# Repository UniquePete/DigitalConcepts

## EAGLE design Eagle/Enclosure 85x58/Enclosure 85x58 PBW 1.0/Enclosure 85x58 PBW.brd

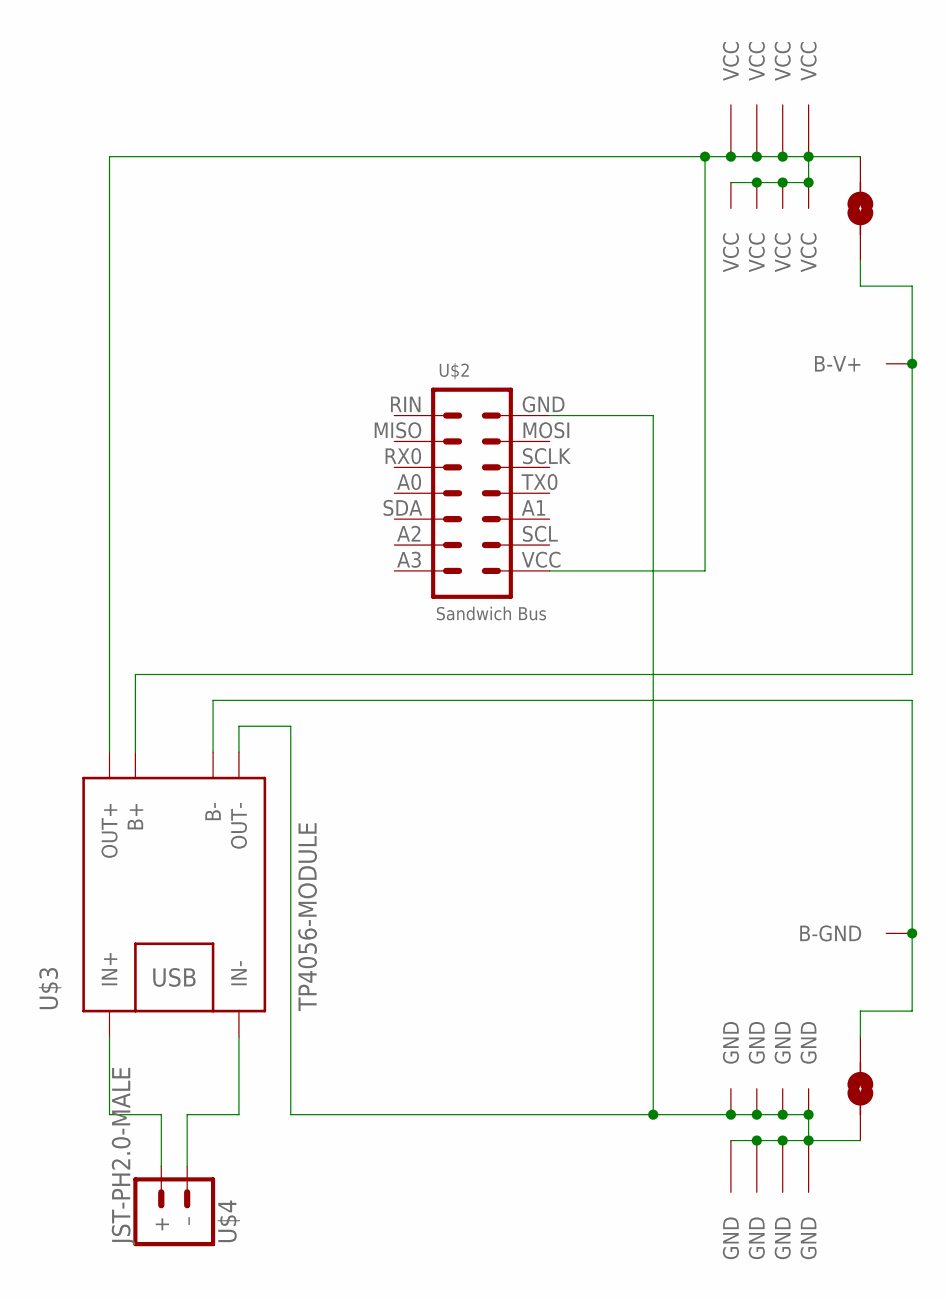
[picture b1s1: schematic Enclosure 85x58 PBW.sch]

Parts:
U$1: PROTO-28X18-BAT2-SJ-W
U$2: Sandwich Bus; CONN_2X7-WIJNAND-PROCESSOR
U$3: TP4056-MODULE; BATTERY-CHARGER-LI-PROT
U$4: JST-PH2.0-MALE; JST-PH2.0

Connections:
GND: U$1.GND@SJ (GND), U$1.P27-11 (GND), U$1.P27-12 (GND), U$1.P27-13 (GND), U$1.P27-14 (GND), U$1.P28-11 (GND), U$1.P28-12 (GND), U$1.P28-13 (GND), U$1.P28-14 (GND), U$2.GND (7), U$3.OUT-
unnamed: U$1.B-GND@SJ (B-GND), U$1.P25-16 (B-GND), U$3.B-
unnamed: U$1.B-V+@SJ (B-V+), U$1.P03-16 (B-V+), U$3.B+
unnamed: U$3.IN+, U$4.+
unnamed: U$3.IN-, U$4.- (–)
VCC: U$1.P01-11 (VCC), U$1.P01-12 (VCC), U$1.P01-13 (VCC), U$1.P01-14 (VCC), U$1.P02-11 (VCC), U$1.P02-12 (VCC), U$1.P02-13 (VCC), U$1.P02-14 (VCC), U$1.VCC@SJ (VCC), U$2.VCC (1), U$3.OUT+

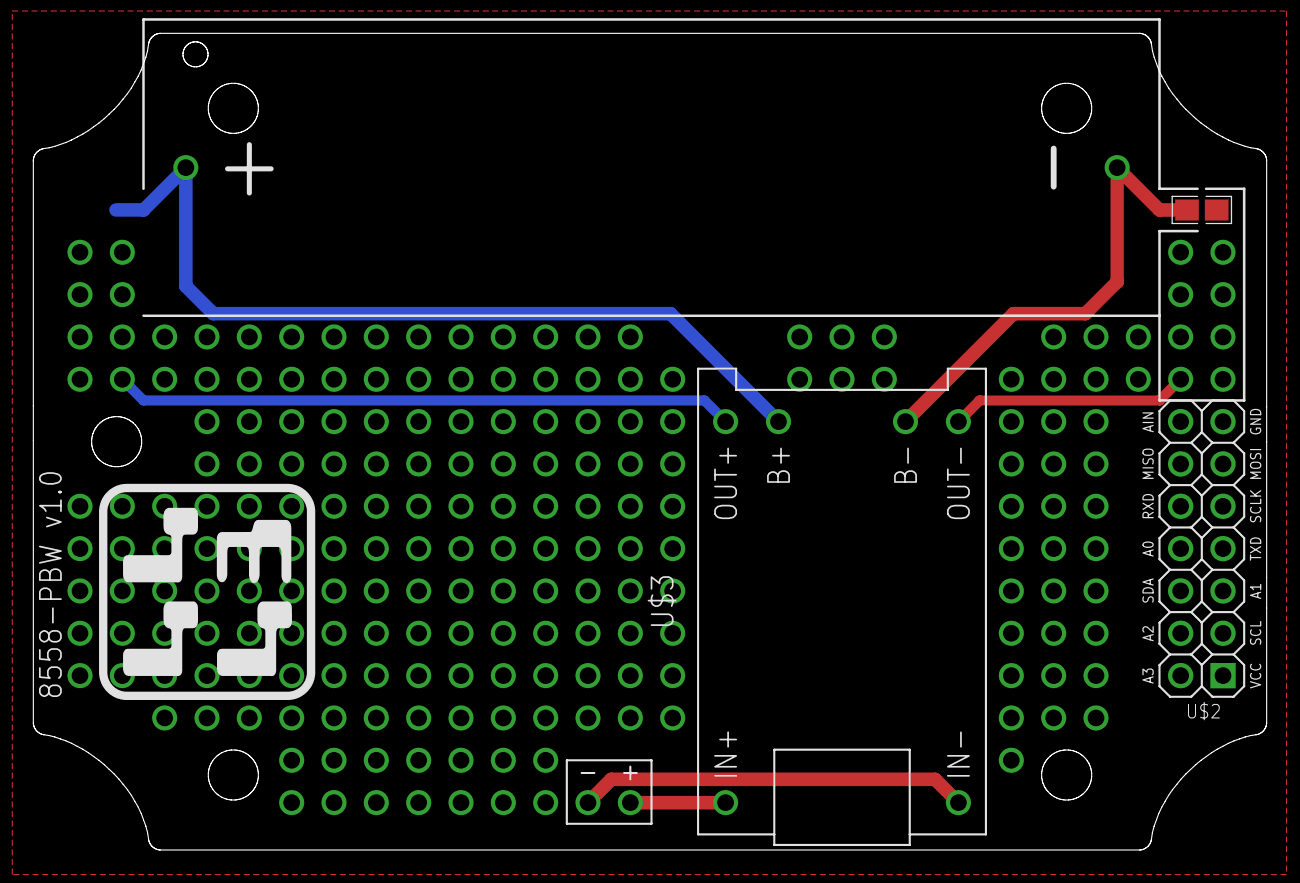
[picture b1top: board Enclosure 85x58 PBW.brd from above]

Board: 2 copper layers, 74.0 x 49.0 mm, 4 parts (0 on the bottom side), 6 nets.

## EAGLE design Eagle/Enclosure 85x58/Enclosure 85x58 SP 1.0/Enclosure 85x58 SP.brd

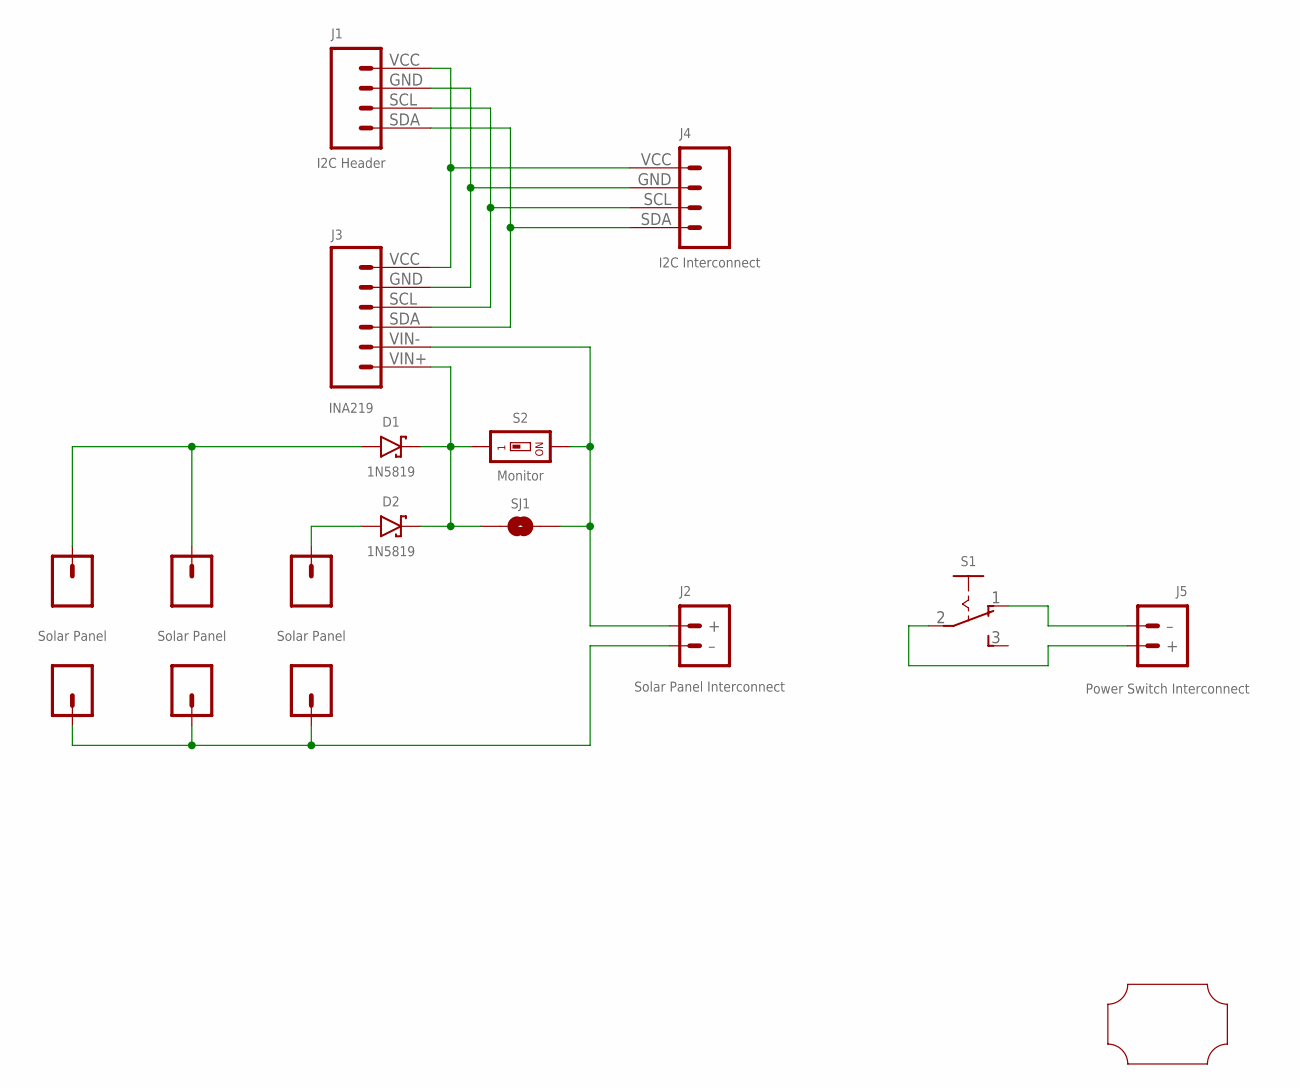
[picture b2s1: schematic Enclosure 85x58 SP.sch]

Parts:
+, +1, +2: Solar Panel; PAD-SMD-GENERIC
-, -1, -2: Solar Panel; PAD-SMD-GENERIC
D1, D2: 1N5819; SOD-123
J1: I2C Header; CONN_04-I2C
J2: Solar Panel Interconnect; JST-PH2.0-2-HORIZONTAL
J3: INA219; CONN_06-INA219
J4: I2C Interconnect; JST-PH2.0-4-HORIZONTAL
J5: Power Switch Interconnect; JST-PH2.0-2-HORIZONTAL
S1: SWITCH-SLIDE-SPDT; SWITCH-SPDT-PTH
S2: Monitor; SMD-001
SJ1: SJ
U$1: PROTO-28X18-SP

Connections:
GND: J1.GND (2), J3.GND (2), J4.GND (3)
unnamed: J1.SDA (4), J3.SDA (4), J4.SDA (1)
unnamed: J1.SCL (3), J3.SCL (3), J4.SCL (2)
unnamed: -.P$1, -1.P$1, -2.P$1, J2.2 (–)
unnamed: J2.1 (+), J3.VIN- (5), S2.2, SJ1.2
unnamed: D1.C, D2.C, J3.VIN+ (6), S2.1, SJ1.1
unnamed: J5.1 (+), S1.2
unnamed: +1.P$1, +2.P$1, D1.A
unnamed: +.P$1, D2.A
unnamed: J5.2 (–), S1.1 (O)
VCC: J1.VCC (1), J3.VCC (1), J4.VCC (4)

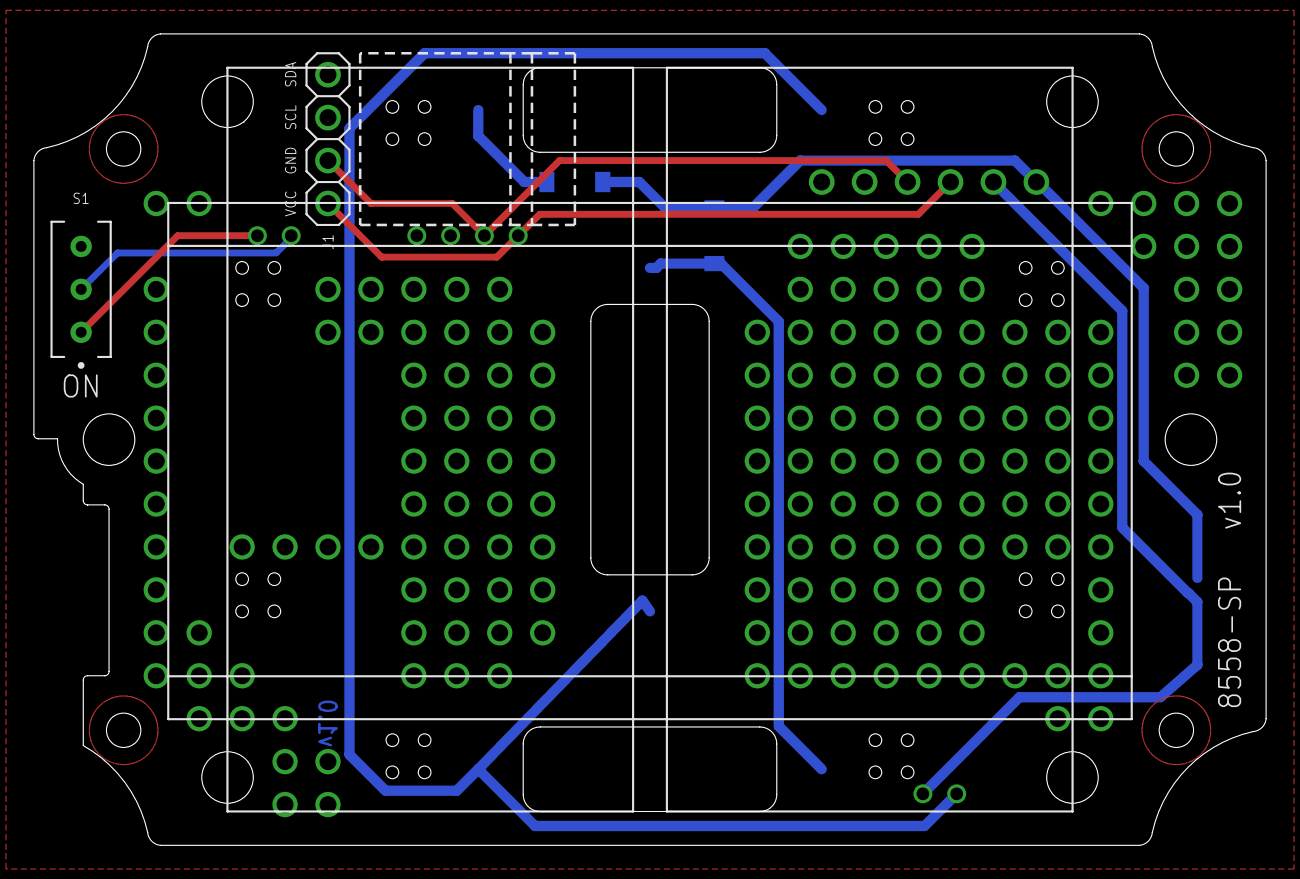
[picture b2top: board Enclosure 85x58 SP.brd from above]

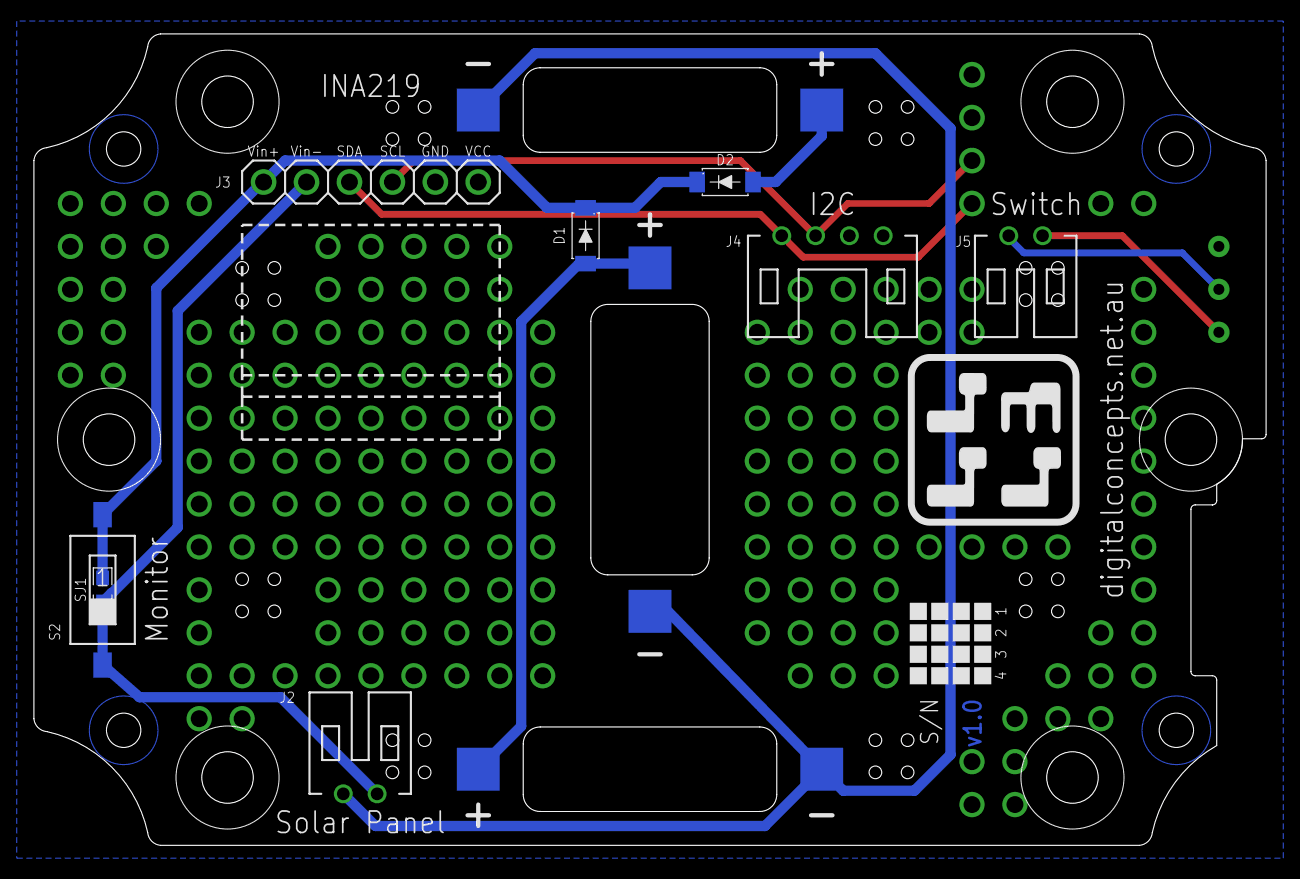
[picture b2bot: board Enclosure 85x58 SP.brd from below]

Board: 2 copper layers, 72.9 x 48.0 mm, 17 parts (14 on the bottom side), 11 nets.

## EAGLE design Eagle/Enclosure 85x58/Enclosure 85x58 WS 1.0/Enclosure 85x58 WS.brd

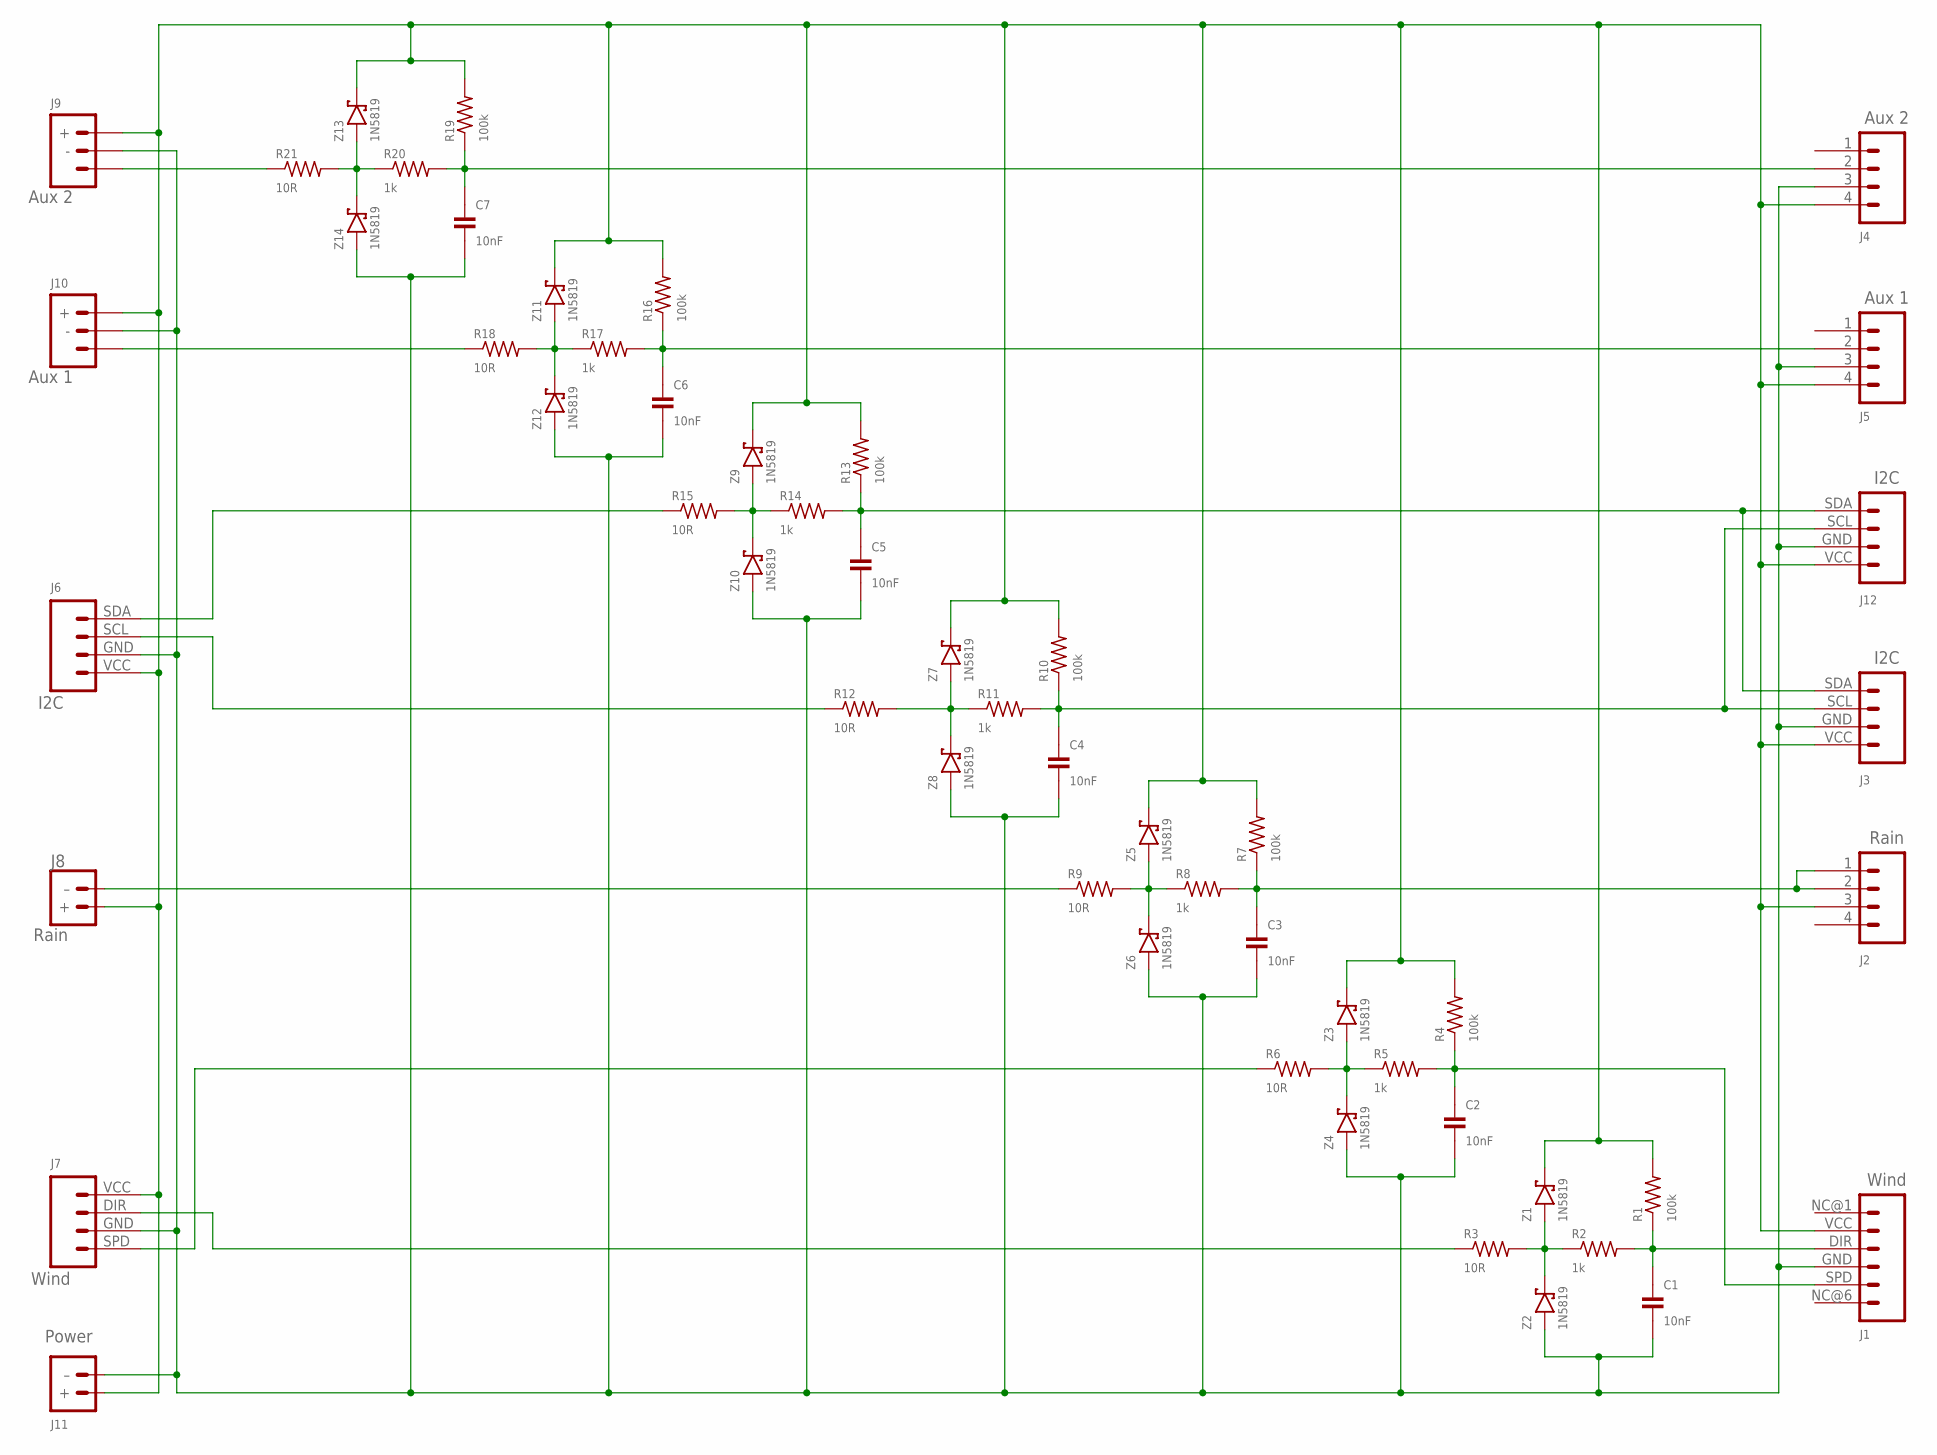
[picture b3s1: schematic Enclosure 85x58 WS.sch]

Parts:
C1, C2, C3, C4, C5, C6, C7: 10nF; C0805-VIA-2
J1: Wind; RJ11-6-VERTICAL-WIND
J2: Rain; RJ11-4-VERTICAL
J3: I2C; RJ11-4-VERTICAL-I2C
J4: Aux 2; RJ11-4-VERTICAL
J5: Aux 1; RJ11-4-VERTICAL
J6: I2C; JST-PH2.0-4-VERTICAL-I2C
J7: Wind; JST-PH2.0-4-VERTICAL-WIND
J8: Rain; JST-PH2.0-2-VERTICAL=POWER
J9: Aux 2; JST-PH2.0-3-VERTICAL
J10: Aux 1; JST-PH2.0-3-VERTICAL
J11: Power; JST-PH2.0-2-VERTICAL=POWER
J12: I2C; CONN_04-I2C
R1, R4, R7, R10, R13, R16, R19: 100k; R0805
R2, R5, R8, R11, R14, R17, R20: 1k; R0805
R3, R6, R9, R12, R15, R18, R21: 10R; R0805-VIA-1
Z1, Z3, Z5, Z7, Z9, Z11, Z13: 1N5819; SOD-123
Z2, Z4, Z6, Z8, Z10, Z12, Z14: 1N5819; SOD-123-VIA-A

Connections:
GND: C1.2, C1.2@VIA (2), C2.2, C2.2@VIA (2), C3.2, C3.2@VIA (2), C4.2, C4.2@VIA (2), C5.2, C5.2@VIA (2), C6.2, C6.2@VIA (2), C7.2, C7.2@VIA (2), J1.GND (4), J3.GND (2), J4.3 (2), J5.3 (2), J6.GND (3), J7.GND (3), J9.-, J10.-, J11.- (–), J12.GND (2), Z2.A, Z2.P$A (A), Z4.A, Z4.P$A (A), Z6.A, Z6.P$A (A), Z8.A, Z8.P$A (A), Z10.A, Z10.P$A (A), Z12.A, Z12.P$A (A), Z14.A, Z14.P$A (A)
unnamed: R14.1, R15.2, Z9.A, Z10.C
unnamed: C2.1, J1.SPD (5), R4.1, R5.2
unnamed: C5.1, J3.SDA (4), J12.SDA (4), R13.1, R14.2
unnamed: J7.DIR (2), R3.1, R3.1@VIA (1)
unnamed: R11.1, R12.2, Z7.A, Z8.C
unnamed: C4.1, J3.SCL (3), J12.SCL (3), R10.1, R11.2
unnamed: R8.1, R9.2, Z5.A, Z6.C
unnamed: J6.SDA (1), R15.1, R15.1@VIA (1)
unnamed: J10.SIG, R18.1, R18.1@VIA (1)
unnamed: J7.SPD (4), R6.1, R6.1@VIA (1)
unnamed: J6.SCL (2), R12.1, R12.1@VIA (1)
unnamed: J9.SIG, R21.1, R21.1@VIA (1)
unnamed: R2.1, R3.2, Z1.A, Z2.C
unnamed: R17.1, R18.2, Z11.A, Z12.C
unnamed: C6.1, J5.2 (3), R16.1, R17.2
unnamed: R20.1, R21.2, Z13.A, Z14.C
unnamed: C7.1, J4.2 (3), R19.1, R20.2
unnamed: C3.1, J2.1 (4), J2.2 (3), R7.1, R8.2
unnamed: C1.1, J1.DIR (3), R1.1, R2.2
unnamed: R5.1, R6.2, Z3.A, Z4.C
unnamed: J8.- (–), R9.1, R9.1@VIA (1)
VCC: J1.VCC (2), J2.3 (2), J3.VCC (1), J4.4 (1), J5.4 (1), J6.VCC (4), J7.VCC (1), J8.+, J9.+, J10.+, J11.+, J12.VCC (1), R1.2, R4.2, R7.2, R10.2, R13.2, R16.2, R19.2, Z1.C, Z3.C, Z5.C, Z7.C, Z9.C, Z11.C, Z13.C

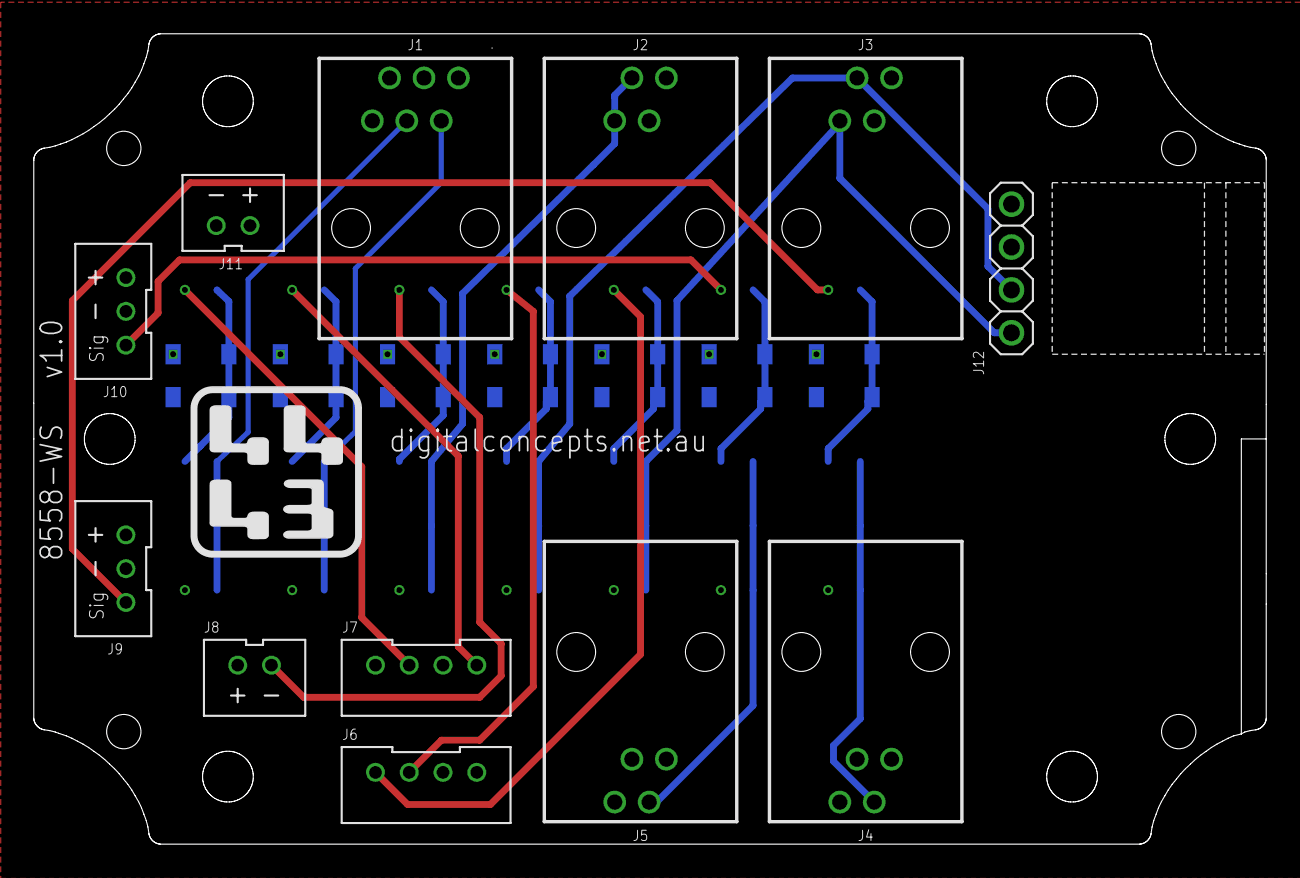
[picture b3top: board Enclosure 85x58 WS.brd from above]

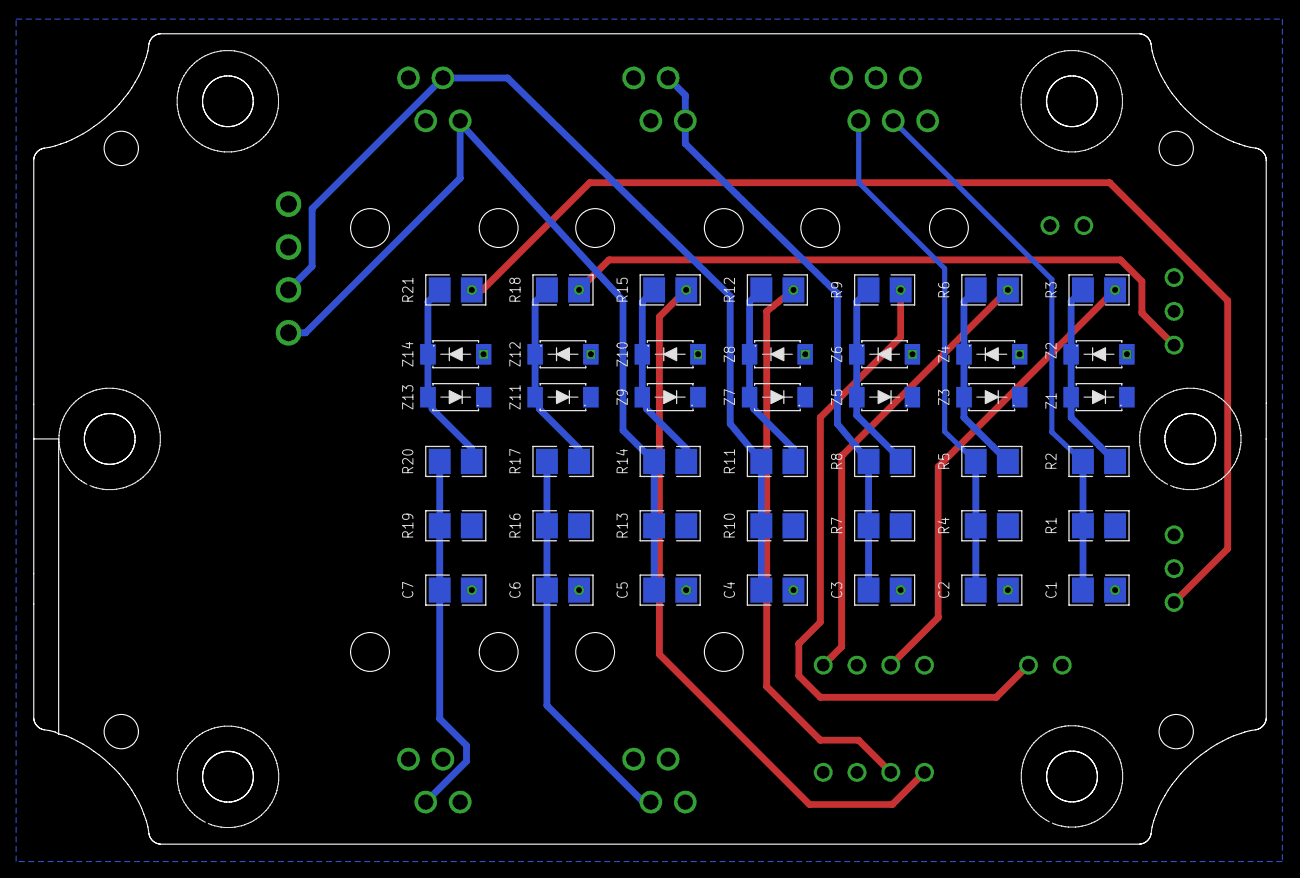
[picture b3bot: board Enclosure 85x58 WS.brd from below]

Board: 2 copper layers, 73.0 x 48.0 mm, 54 parts (42 on the bottom side), 23 nets.
